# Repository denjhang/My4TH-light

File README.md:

# My4TH light
 My4TH light is the big brother of the My4TH XS computer board. In contrast to the My4TH XS it has an I2C interface that is 8 times faster than the I2C interface of the original My4TH board.   
 Originated from: http://mynor.org/my4th_xs.htm

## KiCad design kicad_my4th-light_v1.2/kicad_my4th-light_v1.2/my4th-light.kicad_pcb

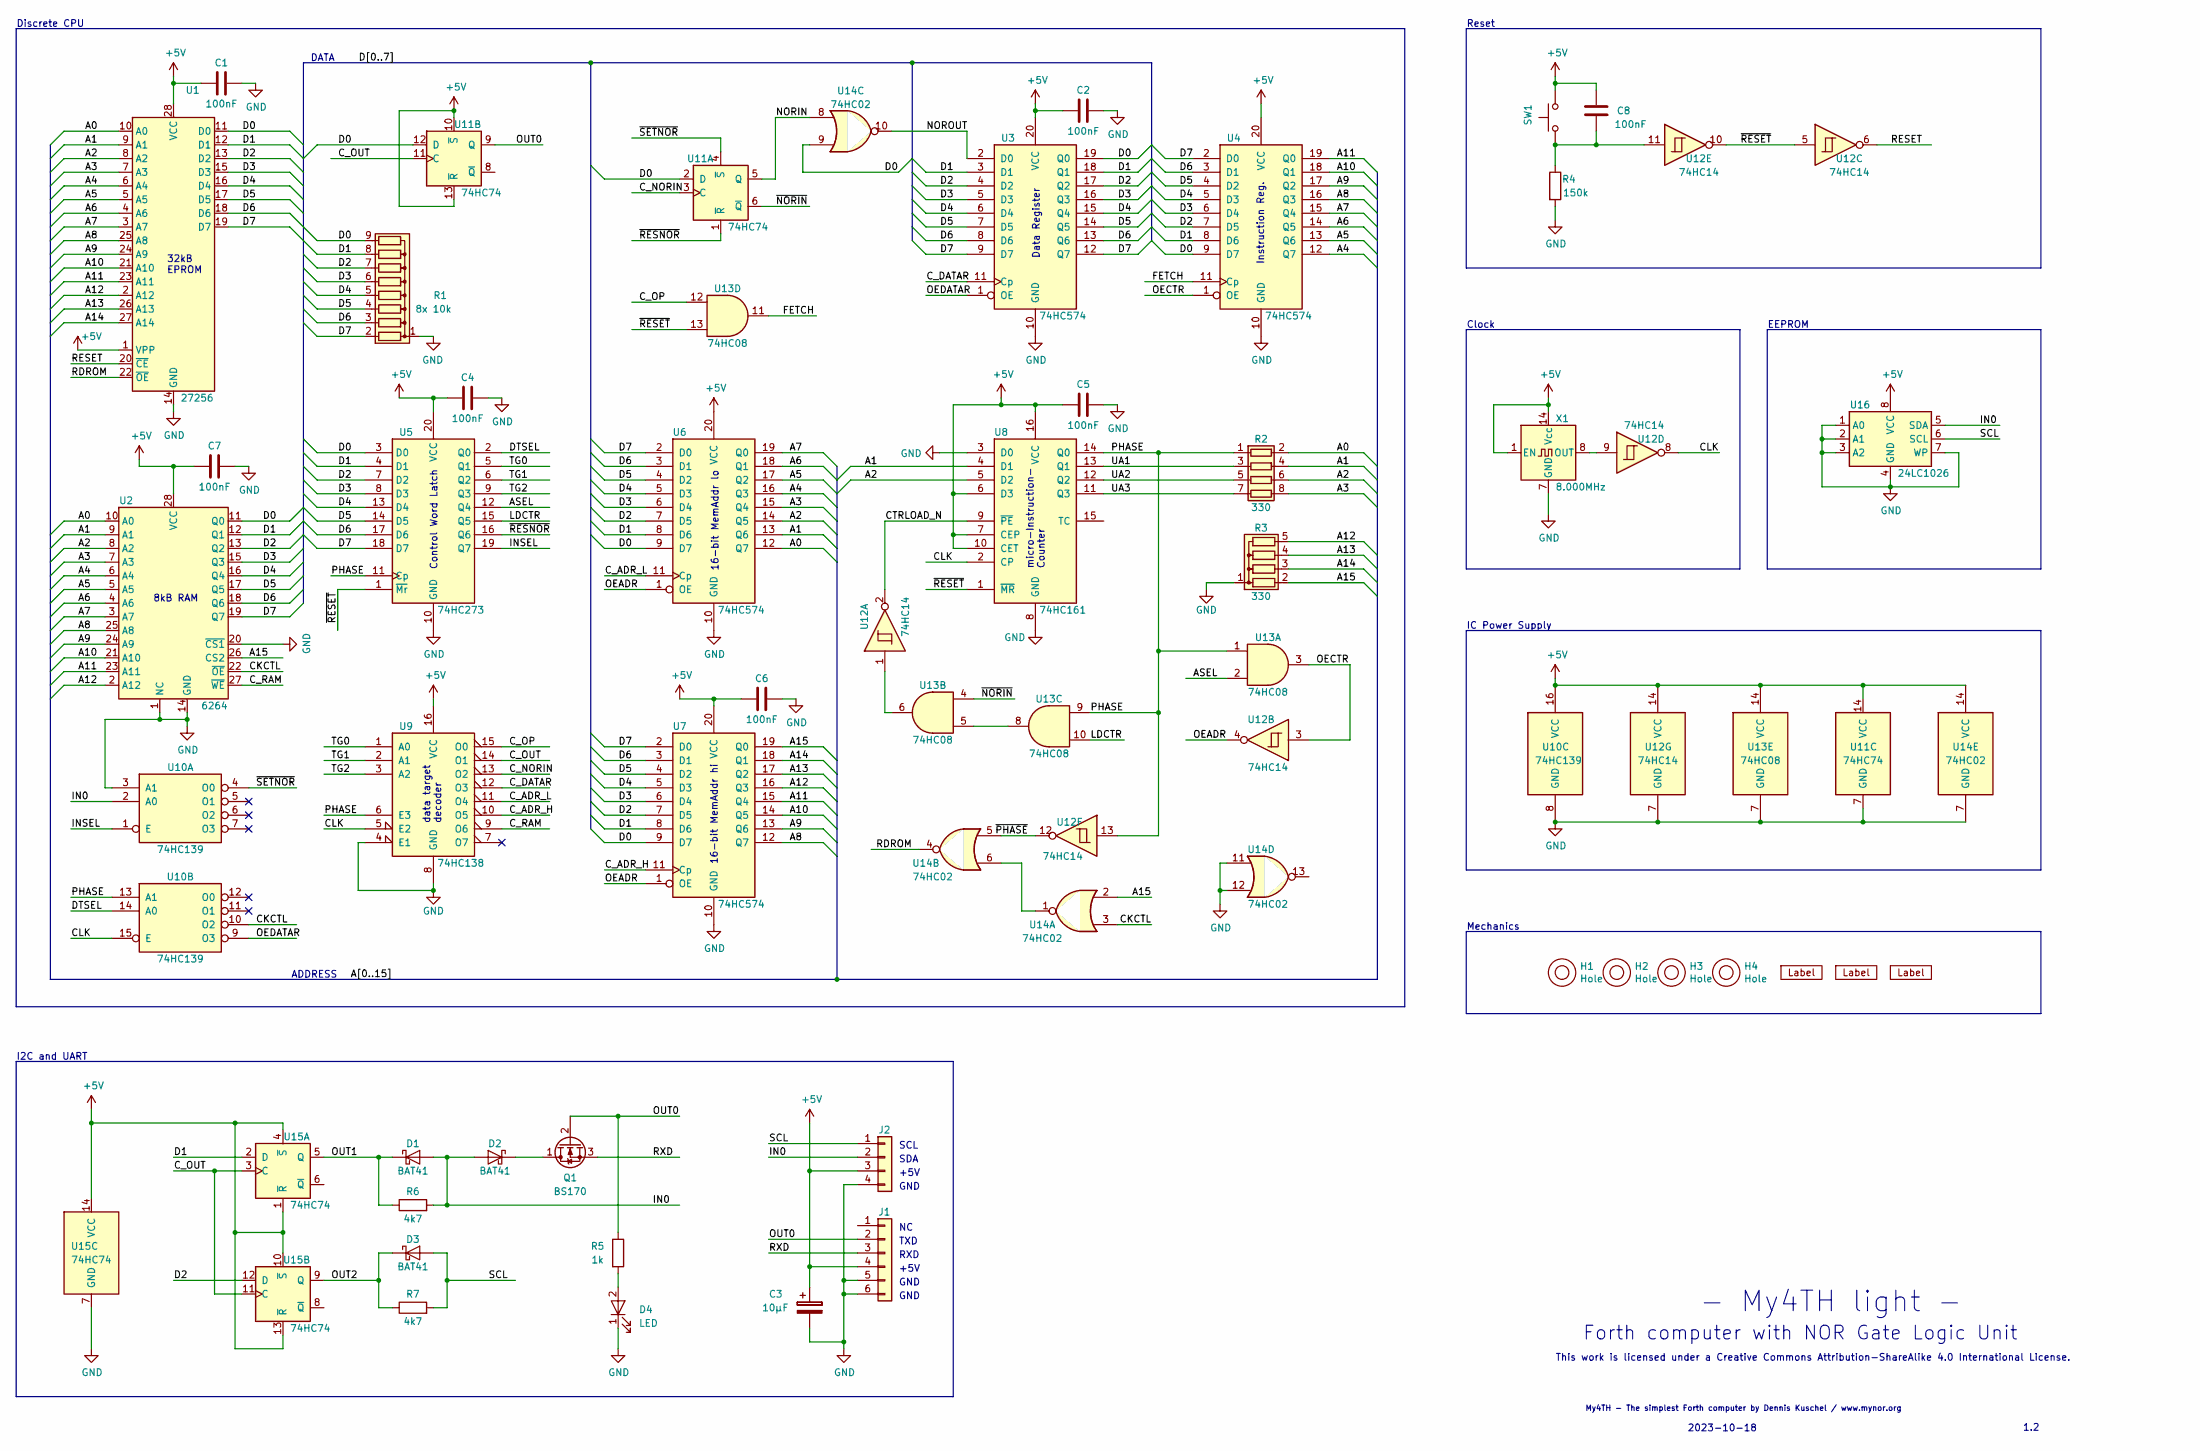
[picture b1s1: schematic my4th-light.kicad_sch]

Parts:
C1, C2, C4, C5, C6, C7, C8: 100nF; C_Disc_D5.0mm_W2.5mm_P5.00mm
C3: 10µF; CP_Radial_D5.0mm_P2.00mm
D1, D2, D3: BAT41; D_DO-35_SOD27_P7.62mm_Horizontal
D4: LED; LED_D3.0mm
H1, H2, H3, H4: Hole; nonplated_hole_drill_2.6mm_dia_5.2mm
J1: Conn_01x06; Pin_Header_Angled_1x06_Pitch2.54mm
J2: Conn_01x04; Pin_Header_Angled_1x04_Pitch2.54mm
LB1: Label; MyNOR-Logo-2
LB2: Label; cc-by-sa
LB3: Label; img-my4th
Q1: BS170; TO-92_Inline_Wide
R1: 8x 10k; R_Array_SIP9
R2: 330; R_Array_SIP8
R3: 330; R_Array_SIP5
R4: 150k; R_Axial_DIN0207_L6.3mm_D2.5mm_P7.62mm_Horizontal
R5: 1k; R_Axial_DIN0207_L6.3mm_D2.5mm_P7.62mm_Horizontal
R6, R7: 4k7; R_Axial_DIN0207_L6.3mm_D2.5mm_P7.62mm_Horizontal
SW1: SW_Push; SW_PUSH_6mm_h4.3mm
U1: 27256; DIP-28_W15.24mm_Socket
U2: 6264; DIP-28_W15.24mm
U3, U4, U6, U7: 74HC574; DIP-20_W7.62mm
U5: 74HC273; DIP-20_W7.62mm
U8: 74HC161; DIP-16_W7.62mm
U9: 74HC138; DIP-16_W7.62mm
U10: 74HC139; DIP-16_W7.62mm
U11, U15: 74HC74; DIP-14_W7.62mm
U12: 74HC14; DIP-14_W7.62mm
U13: 74HC08; DIP-14_W7.62mm
U14: 74HC02; DIP-14_W7.62mm
U16: 24LC1026; DIP-8_W7.62mm
X1: 8.000MHz; Osc_DIP8_DIP14_LargePads

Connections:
+5V: C1.2, C2.2, C3.1, C4.2, C5.2, C6.2, C7.2, C8.2, J1.4, J2.3, SW1.2, U1.1 (VPP), U1.28 (VCC), U2.28 (VCC), U3.20 (VCC), U4.20 (VCC), U5.20 (VCC), U6.20 (VCC), U7.20 (VCC), U8.6 (D3), U8.7 (CEP), U8.10 (CET), U8.16 (VCC), U9.16 (VCC), U10.16 (VCC), U11.10 (~S), U11.13 (~R), U11.14 (VCC), U12.14 (VCC), U13.14 (VCC), U14.14 (VCC), U15.1 (~R), U15.4 (~S), U15.10 (~S), U15.13 (~R), U15.14 (VCC), U16.8 (VCC), X1.1 (EN), X1.14 (Vcc)
/A0: R2.2 (R1.2), U1.10 (A0), U2.10 (A0), U6.12 (Q7)
/A1: R2.4 (R2.2), U1.9 (A1), U2.9 (A1), U6.13 (Q6), U8.4 (D1)
/A2: R2.6 (R3.2), U1.8 (A2), U2.8 (A2), U6.14 (Q5), U8.5 (D2)
/A3: R2.8 (R4.2), U1.7 (A3), U2.7 (A3), U6.15 (Q4)
/A4: U1.6 (A4), U2.6 (A4), U4.12 (Q7), U6.16 (Q3)
/A5: U1.5 (A5), U2.5 (A5), U4.13 (Q6), U6.17 (Q2)
/A6: U1.4 (A6), U2.4 (A6), U4.14 (Q5), U6.18 (Q1)
/A7: U1.3 (A7), U2.3 (A7), U4.15 (Q4), U6.19 (Q0)
/A8: U1.25 (A8), U2.25 (A8), U4.16 (Q3), U7.12 (Q7)
/A9: U1.24 (A9), U2.24 (A9), U4.17 (Q2), U7.13 (Q6)
/A10: U1.21 (A10), U2.21 (A10), U4.18 (Q1), U7.14 (Q5)
/A11: U1.23 (A11), U2.23 (A11), U4.19 (Q0), U7.15 (Q4)
/A12: R3.5 (R4), U1.2 (A12), U2.2 (A12), U7.16 (Q3)
/A13: R3.4 (R3), U1.26 (A13), U7.17 (Q2)
/A14: R3.3 (R2), U1.27 (A14), U7.18 (Q1)
/A15: R3.2 (R1), U2.26 (CS2), U7.19 (Q0), U14.2
/ASEL: U5.12 (Q4), U13.2
/CKCTL: U2.22 (~OE), U10.10 (O2), U14.3
/CLK: U8.2 (CP), U9.5 (E2), U10.15 (E), U12.8
/CTRLOAD_N: U8.9 (~PE), U12.2
/C_ADR_H: U7.11 (Cp), U9.10 (O5)
/C_ADR_L: U6.11 (Cp), U9.11 (O4)
/C_DATAR: U3.11 (Cp), U9.12 (O3)
/C_NORIN: U9.13 (O2), U11.3 (C)
/C_OP: U9.15 (O0), U13.12
/C_OUT: U9.14 (O1), U11.11 (C), U15.3 (C), U15.11 (C)
/C_RAM: U2.27 (~WE), U9.9 (O6)
/D0: R1.9 (R8), U1.11 (D0), U2.11 (Q0), U3.19 (Q0), U4.9 (D7), U5.3 (D0), U6.9 (D7), U7.9 (D7), U11.2 (D), U11.12 (D), U14.9
/D1: R1.8 (R7), U1.12 (D1), U2.12 (Q1), U3.3 (D1), U3.18 (Q1), U4.8 (D6), U5.4 (D1), U6.8 (D6), U7.8 (D6), U15.2 (D)
/D2: R1.7 (R6), U1.13 (D2), U2.13 (Q2), U3.4 (D2), U3.17 (Q2), U4.7 (D5), U5.7 (D2), U6.7 (D5), U7.7 (D5), U15.12 (D)
/D3: R1.6 (R5), U1.15 (D3), U2.15 (Q3), U3.5 (D3), U3.16 (Q3), U4.6 (D4), U5.8 (D3), U6.6 (D4), U7.6 (D4)
/D4: R1.5 (R4), U1.16 (D4), U2.16 (Q4), U3.6 (D4), U3.15 (Q4), U4.5 (D3), U5.13 (D4), U6.5 (D3), U7.5 (D3)
/D5: R1.4 (R3), U1.17 (D5), U2.17 (Q5), U3.7 (D5), U3.14 (Q5), U4.4 (D2), U5.14 (D5), U6.4 (D2), U7.4 (D2)
/D6: R1.3 (R2), U1.18 (D6), U2.18 (Q6), U3.8 (D6), U3.13 (Q6), U4.3 (D1), U5.17 (D6), U6.3 (D1), U7.3 (D1)
/D7: R1.2 (R1), U1.19 (D7), U2.19 (Q7), U3.9 (D7), U3.12 (Q7), U4.2 (D0), U5.18 (D7), U6.2 (D0), U7.2 (D0)
/DTSEL: U5.2 (Q0), U10.14 (A0)
/FETCH: U4.11 (Cp), U13.11
/IN0: D1.2 (A), D2.2 (A), J2.2, R6.2, U10.2 (A0), U16.5 (SDA)
/INSEL: U5.19 (Q7), U10.1 (E)
/LDCTR: U5.15 (Q5), U13.10
/NORIN: U11.5 (Q), U14.8
/NOROUT: U3.2 (D0), U14.10
/OEADR: U6.1 (OE), U7.1 (OE), U12.4
/OECTR: U4.1 (OE), U12.3, U13.3
/OEDATAR: U3.1 (OE), U10.9 (O3)
/OUT0: J1.2, Q1.2 (G), R5.1, U11.9 (Q)
/OUT1: D1.1 (K), R6.1, U15.5 (Q)
/OUT2: D3.1 (K), R7.1, U15.9 (Q)
/PHASE: R2.1 (R1.1), U5.11 (Cp), U8.14 (Q0), U9.6 (E3), U10.13 (A1), U12.13, U13.1, U13.9
/RDROM: U1.22 (~OE), U14.4
/RESET: U1.20 (~CE), U12.6
/RXD: J1.3, Q1.3 (S)
/SCL: D3.2 (A), J2.1, R7.2, U16.6 (SCL)
/TG0: U5.5 (Q1), U9.1 (A0)
/TG1: U5.6 (Q2), U9.2 (A1)
/TG2: U5.9 (Q3), U9.3 (A2)
/UA1: R2.3 (R2.1), U8.13 (Q1)
/UA2: R2.5 (R3.1), U8.12 (Q2)
/UA3: R2.7 (R4.1), U8.11 (Q3)
/~NORIN: U11.6 (~Q), U13.4
/~PHASE: U12.12, U14.5
/~RESET: U5.1 (~Mr), U8.1 (~MR), U12.5, U12.10, U13.13
/~RESNOR: U5.16 (Q6), U11.1 (~R)
/~SETNOR: U10.4 (O0), U11.4 (~S)
GND: C1.1, C2.1, C3.2, C4.1, C5.1, C6.1, C7.1, D4.1 (K), J1.5, J1.6, J2.4, R1.1 (common), R3.1 (common), R4.2, U1.14 (GND), U2.1 (NC), U2.14 (GND), U2.20 (~CS1), U3.10 (GND), U4.10 (GND), U5.10 (GND), U6.10 (GND), U7.10 (GND), U8.3 (D0), U8.8 (GND), U9.4 (E1), U9.8 (GND), U10.3 (A1), U10.8 (GND), U11.7 (GND), U12.7 (GND), U13.7 (GND), U14.7 (GND), U14.11, U14.12, U15.7 (GND), U16.1 (A0), U16.2 (A1), U16.3 (A2), U16.4 (GND), U16.7 (WP), X1.7 (GND)
unnamed: C8.1, R4.1, SW1.1, U12.11
unnamed: D2.1 (K), Q1.1 (D)
unnamed: D4.2 (A), R5.2
unnamed: U12.1, U13.6
unnamed: U13.5, U13.8
unnamed: U14.1, U14.6
unnamed: U12.9, X1.8 (OUT)

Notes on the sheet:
Clock
EEPROM
SDA
Reset
Discrete CPU
data target decoder
DATA
+5V
My4TH - The simplest Forth computer by Dennis Kuschel / www.mynor.org
GND
RXD
Control Word Latch
16-bit MemAddr hi
2023-10-18
ADDRESS
16-bit MemAddr lo
- My4TH light -
IC Power Supply
TXD
1.2
Data Register
micro-Instruction- Counter
This work is licensed under a Creative Commons Attribution-ShareAlike 4.0 International License.
32kB EPROM
I2C and UART
Instruction Reg.
Mechanics
8kB RAM
SCL
Forth computer with NOR Gate Logic Unit

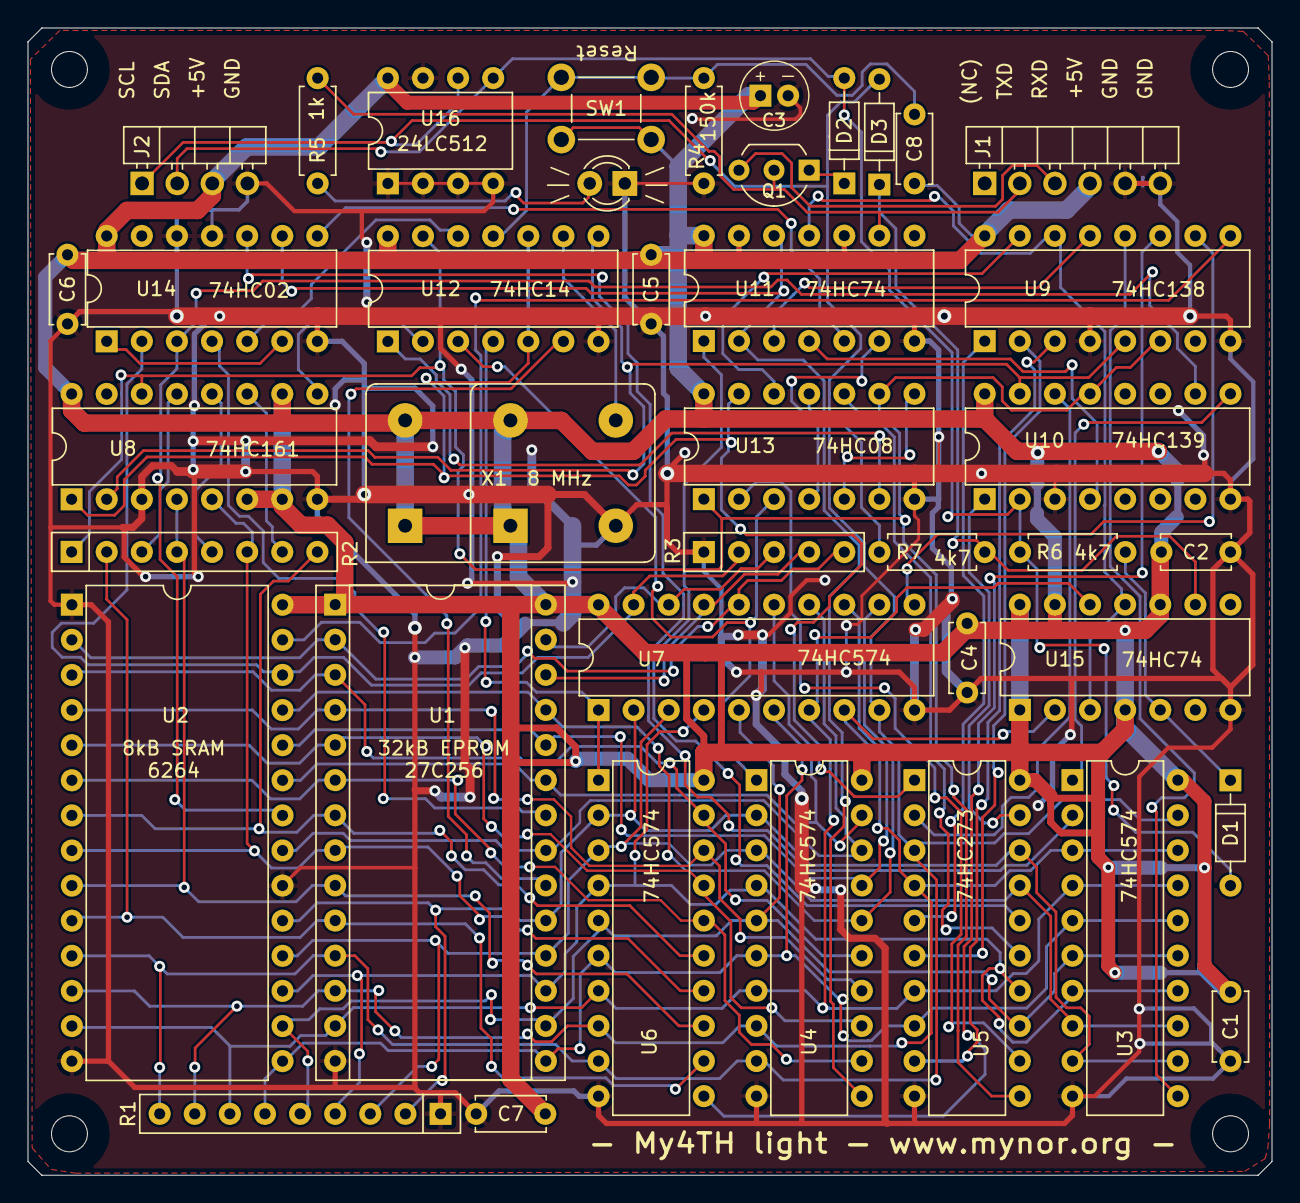
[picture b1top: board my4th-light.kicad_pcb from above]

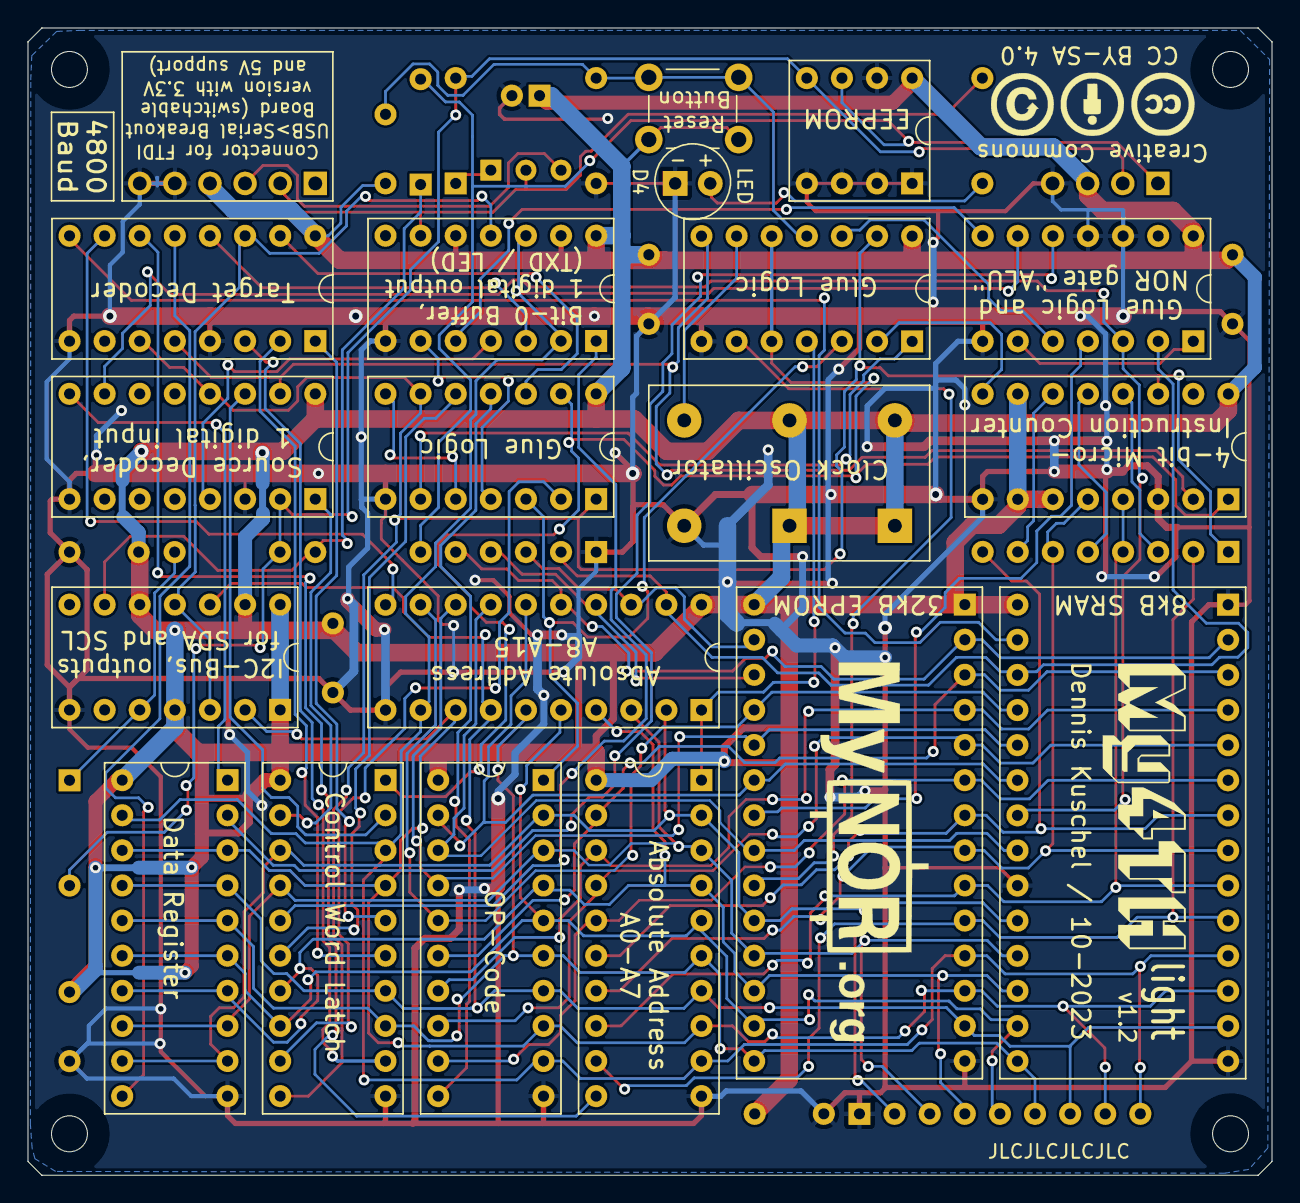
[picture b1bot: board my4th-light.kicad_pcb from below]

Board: 2 copper layers, 90.0 x 83.0 mm, 47 parts (3 on the bottom side), 73 nets.

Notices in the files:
kicad_my4th-light_v1.2/kicad_my4th-light_v1.2/my4th-light.kicad_pcb:
CC BY-SA 4.0
